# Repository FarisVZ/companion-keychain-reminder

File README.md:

# companion-keychain-reminder

a keychain to help poeple with disability that requires reminders every few hours, it also a little companion with oled display face that can be put on belt loop

# Work In Progress...

## Timeline

### June 22th 2025

**The first version on the project**
the first design was just a simple design to make a minimum req for esp12F to work and 3.3v regulator.

### June 26th 2025

Changing some layout and adding more component to the board, that include:

- vibrator motor module
- oled display

### June 29th 2025

Adding 2 button for RST and Boot

### June 30th 2025

Trying to make version 2 by rerouting everything and uses bigger component

### July 4th 2025

try to test it with real component and breadboard and find several issue:

- the module doesnt get enough current from the esp so it need a transistor
- only had few gpio to work with (3 for button, 1 for vibrator, and 2 for 12c address)

### July 5th 2025

trying the prototyping again to find another issue, by tweak something:

- adding a menu to oled display
- temporarily change to buzzer for the vibrator
- change into just two button for navigating up and down and implementing press both button to select menu

### July 8th 2025

- adding RTC to prototype
- adding 2n222 transistor so it can run the vibrator module
- go back use 3 button to navigating (up, down, select)
- add time in menu

### July 21th 2025

- adding pcf8574 ic into pcb to solve lack of gpio problem
- trying to just use ds3231 ic insted of module to make this project smaller
- adding 5 button to navigate

### August 5th 2025

Making a github repo documentation about this project

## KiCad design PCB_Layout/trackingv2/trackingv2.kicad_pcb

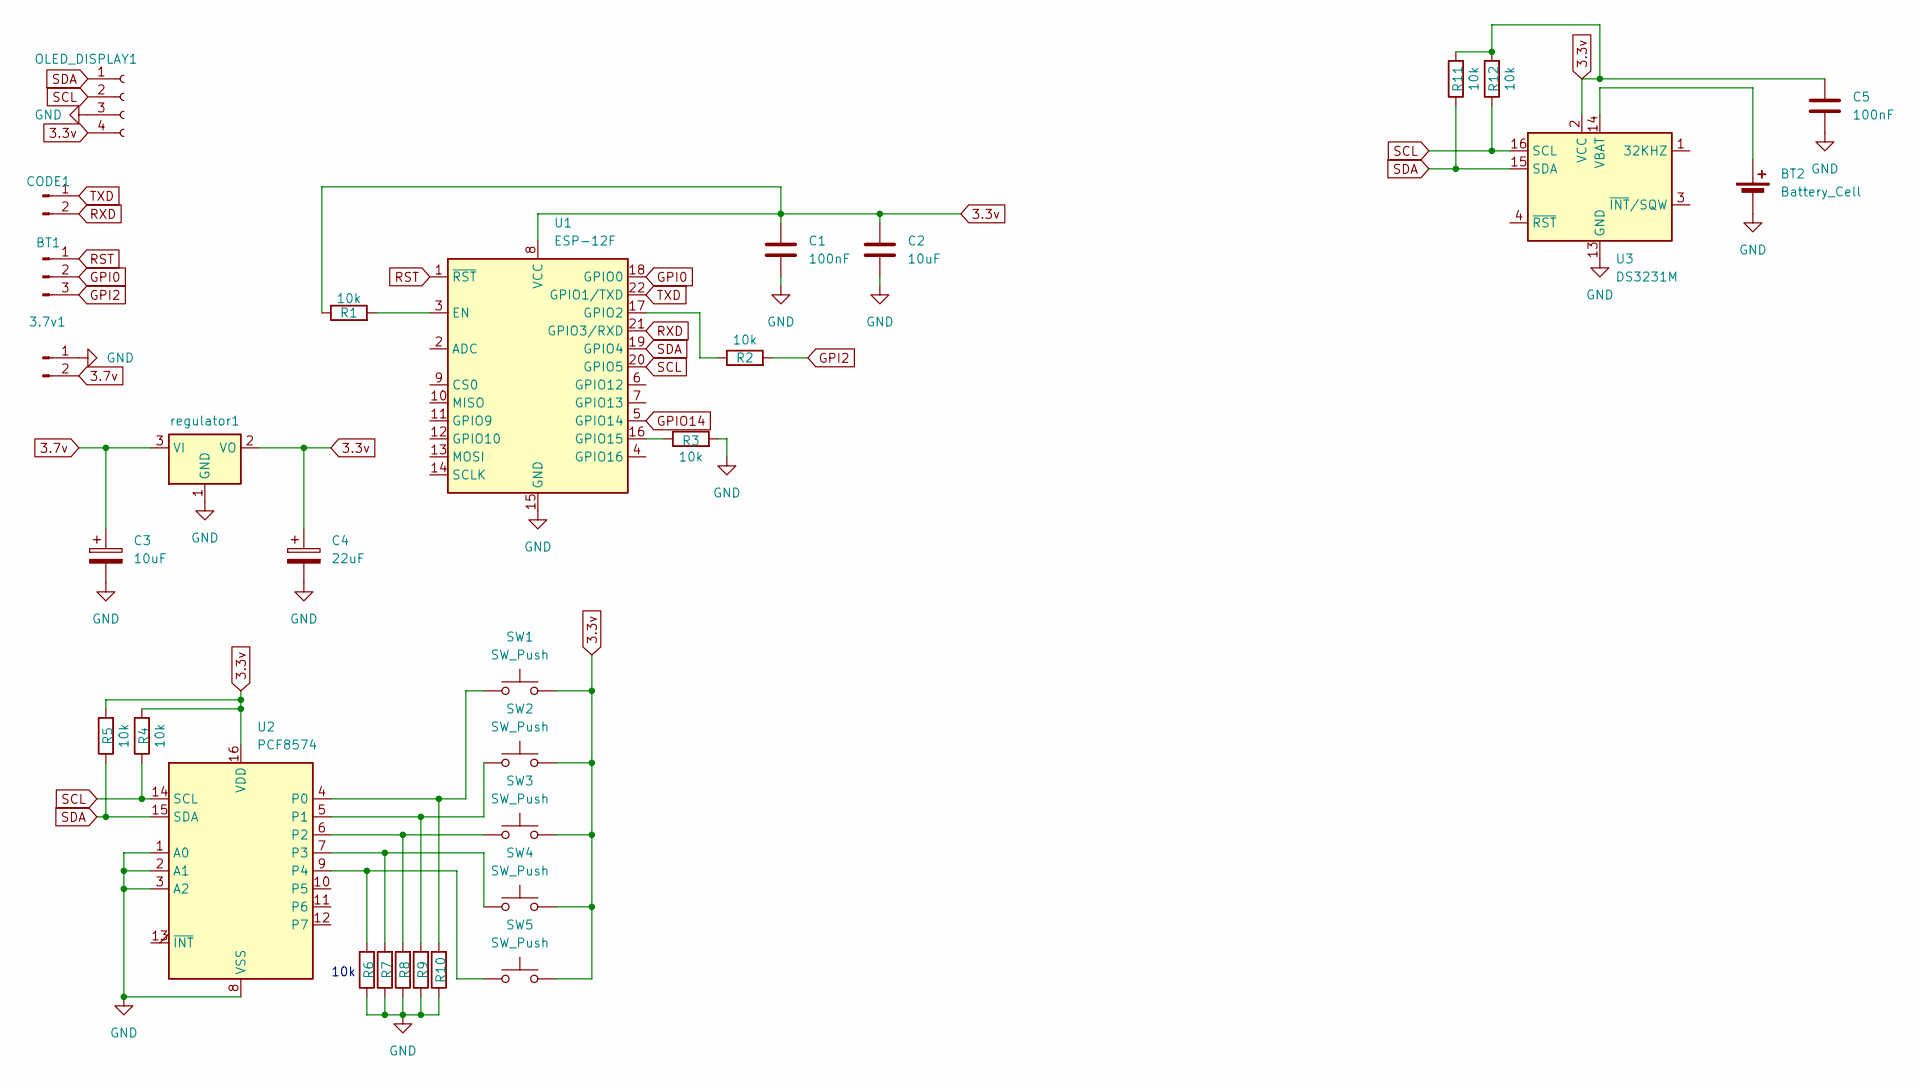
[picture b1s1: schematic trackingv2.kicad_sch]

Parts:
3.7v1: LiPo; PinHeader_1x02_P2.54mm_Vertical
BT1: Conn_01x03_Pin; PinHeader_1x03_P2.54mm_Vertical
BT2: Battery_Cell; BatteryHolder_Keystone_103_1x20mm
C1, C5: 100nF; C_0805_2012Metric_Pad1.18x1.45mm_HandSolder
C2: 10uF; C_0805_2012Metric_Pad1.18x1.45mm_HandSolder
C3: 10uF; CP_EIA-3528-15_AVX-H_Pad1.50x2.35mm_HandSolder
C4: 22uF; CP_EIA-3528-15_AVX-H_Pad1.50x2.35mm_HandSolder
CODE1: Conn_01x02_Pin; PinHeader_1x02_P2.54mm_Vertical
OLED_DISPLAY1: Conn_01x04_Socket; PinSocket_1x04_P2.54mm_Vertical
R1, R2, R3, R4, R5, R11, R12: 10k; R_0805_2012Metric_Pad1.20x1.40mm_HandSolder
R6, R7, R8, R9, R10: 10K; R_0805_2012Metric_Pad1.20x1.40mm_HandSolder
SW1, SW2, SW3, SW4, SW5: SW_Push; SW_PUSH_6mm
U1: ESP-12F; ESP-12E
U2: PCF8574; SOIC-16_3.9x9.9mm_P1.27mm
U3: DS3231M; SOIC-16W_7.5x10.3mm_P1.27mm
regulator1: SOT-223-3_TabPin2

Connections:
3.3v: C1.1, C2.1, C4.1, C5.1, OLED_DISPLAY1.4, R1.1, R4.2, R5.2, R11.2, R12.2, SW1.2, SW2.2, SW3.2, SW4.2, SW5.2, U1.8 (VCC), U2.16 (VDD), U3.2 (VCC), regulator1.2 (VO)
3.7v: 3.7v1.2, C3.1, regulator1.3 (VI)
GND: 3.7v1.1, BT2.2 (-), C1.2, C2.2, C3.2, C4.2, C5.2, OLED_DISPLAY1.3, R3.2, R6.1, R7.1, R8.1, R9.1, R10.1, U1.15 (GND), U2.1 (A0), U2.2 (A1), U2.3 (A2), U2.8 (VSS), U3.5 (GND), U3.6 (GND), U3.7 (GND), U3.8 (GND), U3.9 (GND), U3.10 (GND), U3.11 (GND), U3.12 (GND), U3.13 (GND), regulator1.1 (GND)
GPI0: BT1.2, U1.18 (GPIO0)
GPI2: BT1.3, R2.2
GPIO14: U1.5 (GPIO14)
unnamed: BT2.1 (+), U3.14 (VBAT)
unnamed: R1.2, U1.3 (EN)
unnamed: R2.1, U1.17 (GPIO2)
unnamed: R3.1, U1.16 (GPIO15)
unnamed: R10.2, SW1.1, U2.4 (P0)
unnamed: R9.2, SW2.1, U2.5 (P1)
unnamed: R8.2, SW3.1, U2.6 (P2)
unnamed: R7.2, SW4.1, U2.7 (P3)
unnamed: R6.2, SW5.1, U2.9 (P4)
RST: BT1.1, U1.1 (~RST)
RXD: CODE1.2, U1.21 (GPIO3/RXD)
SCL: OLED_DISPLAY1.2, R4.1, R12.1, U1.20 (GPIO5), U2.14 (SCL), U3.16 (SCL)
SDA: OLED_DISPLAY1.1, R5.1, R11.1, U1.19 (GPIO4), U2.15 (SDA), U3.15 (SDA)
TXD: CODE1.1, U1.22 (GPIO1/TXD)

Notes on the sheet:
10k

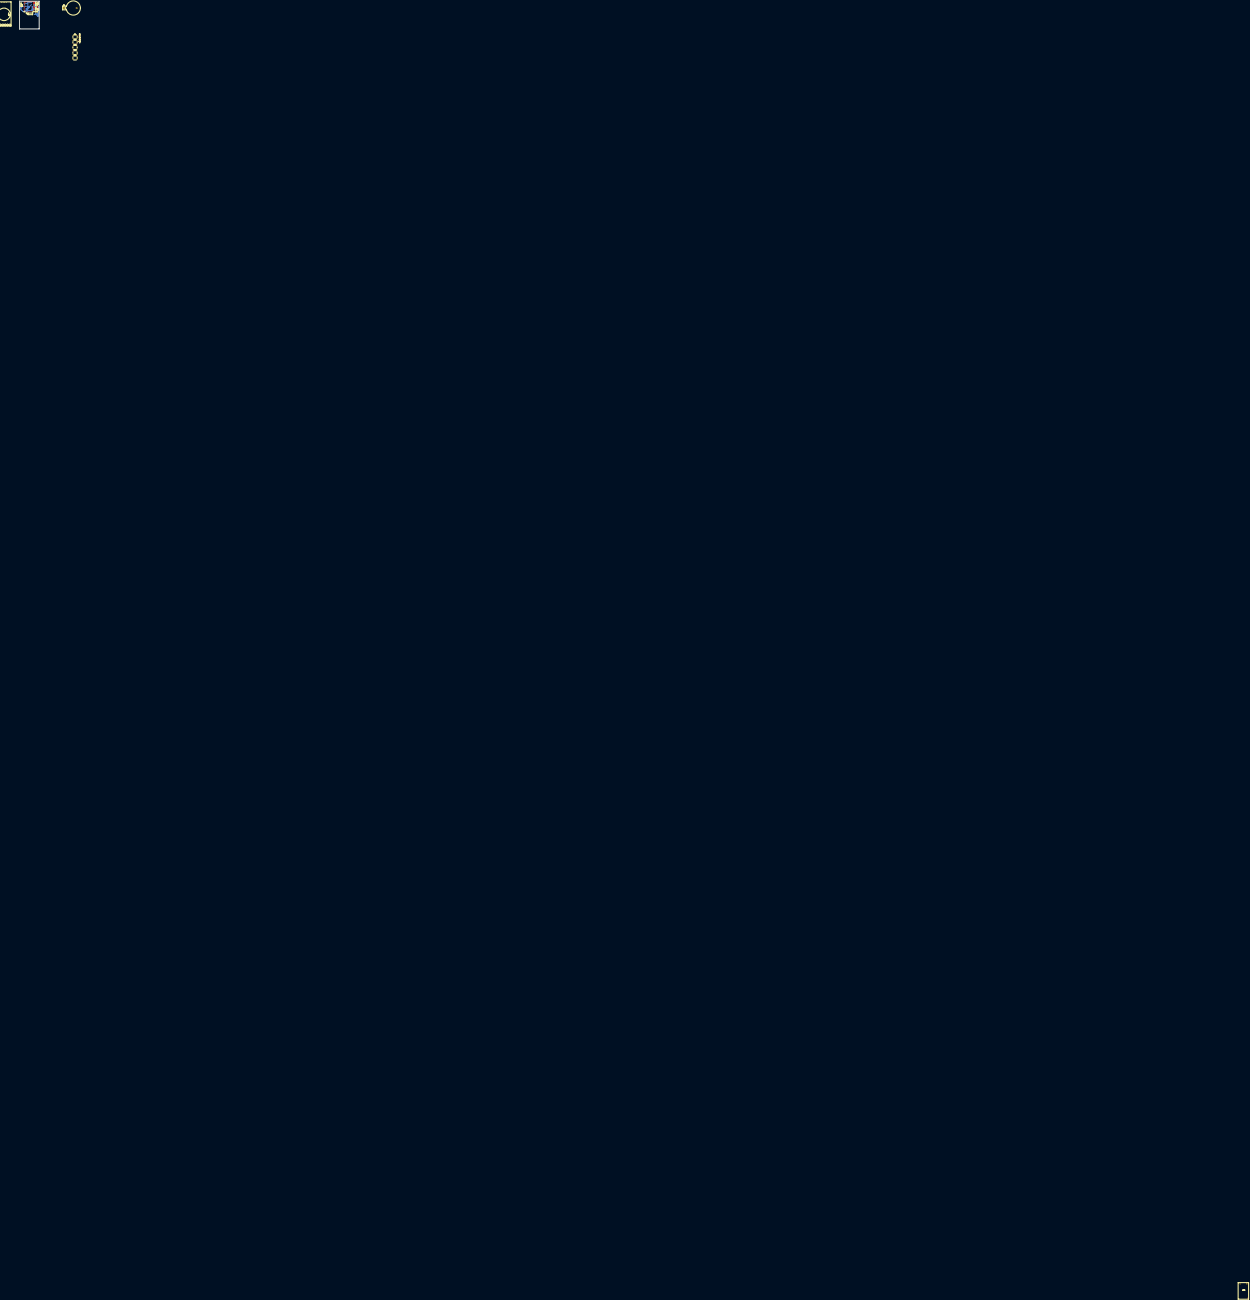
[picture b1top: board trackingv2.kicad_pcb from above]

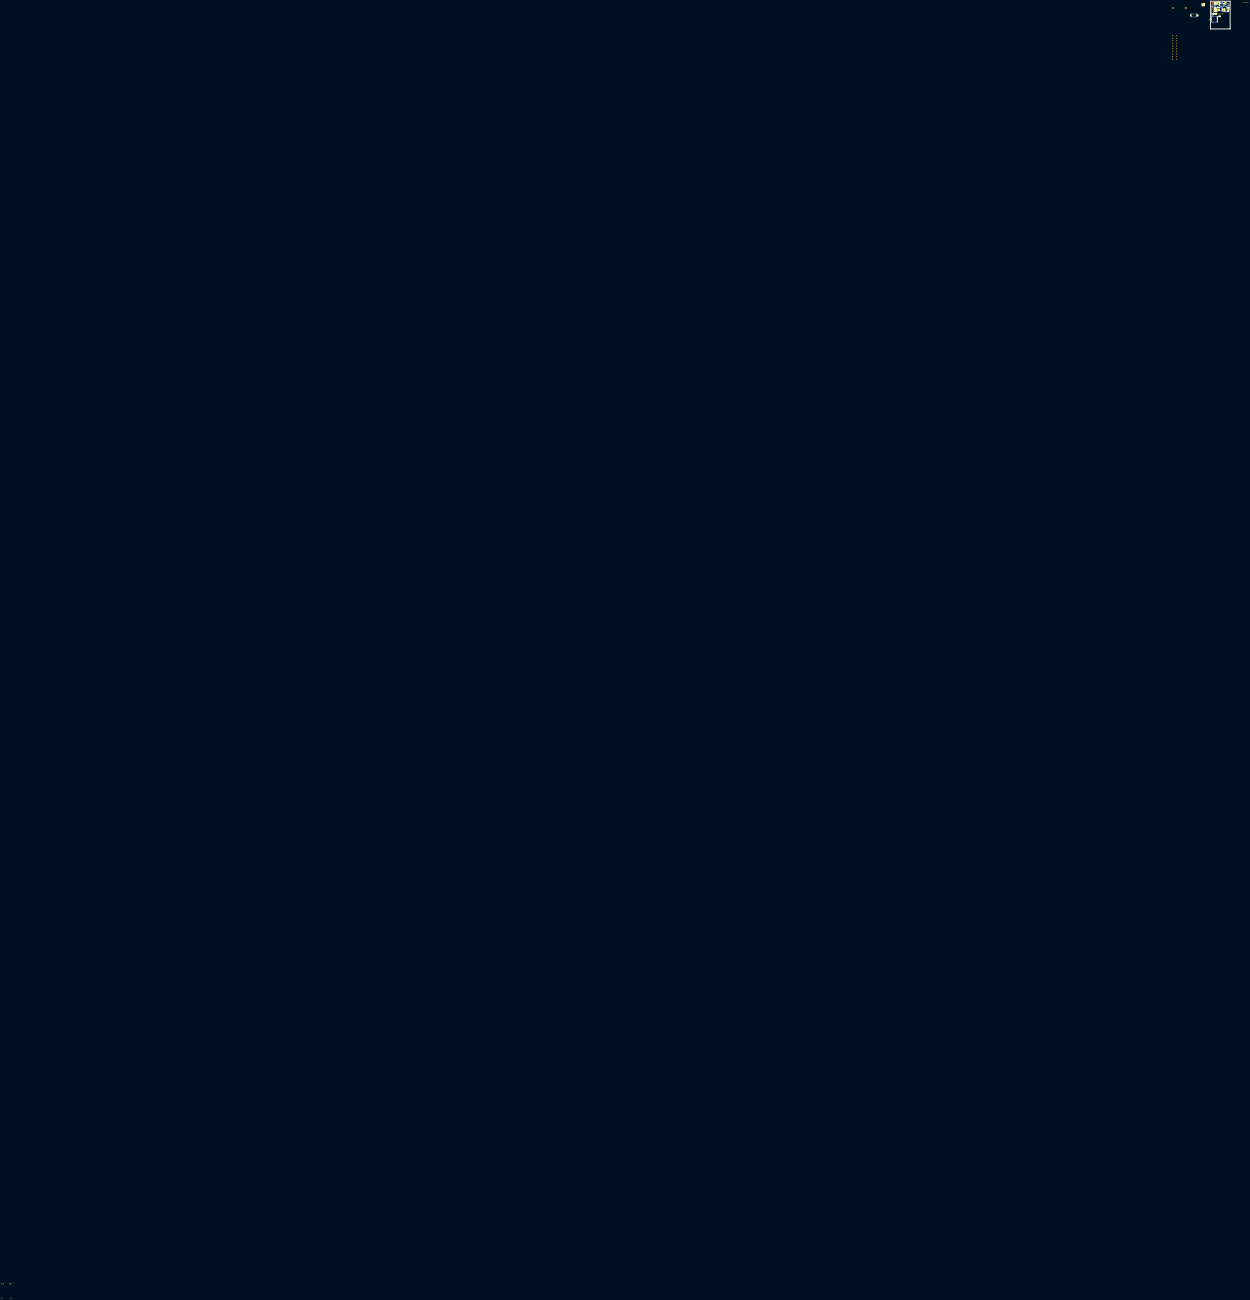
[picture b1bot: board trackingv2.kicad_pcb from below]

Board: 2 copper layers, 32.0 x 45.0 mm, 31 parts (15 on the bottom side), 19 nets.

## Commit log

2025-07-27 README.md
2025-08-02 add progress
2025-08-05 add pcb kicad layout
2025-08-05 add timeline
2025-08-05 adding more timeline
2025-08-05 fixing the readme
2025-08-05 adding july 21
2025-08-05 add 5 august
